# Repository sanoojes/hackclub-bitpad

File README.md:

# BitPad

A simple, customizable macropad with hot swapable keys, fully programmable keys, per-key RGB
lighting, multiple profiles for gaming, programming, editing, and more. uses QMK Firmware

## CAD

## PCB

## Firmware

Firmware available at [firmware/](firmware/) firmware will be tweaked and updated after i get the materials.

## BOM (Bill of materials)

Here's what I used for the device:

- 1x XIAO_RP2040 module
- 1x SK6812 Mini LEDs
- 1x EC11 Rotary Encoder
- 4x M3x16mm screws
- 4x M3x5mmx4mm inserts
- 16x Cherry MX Hotswappable Switches
- 16x DSA Keycaps
- 3D Printed Case

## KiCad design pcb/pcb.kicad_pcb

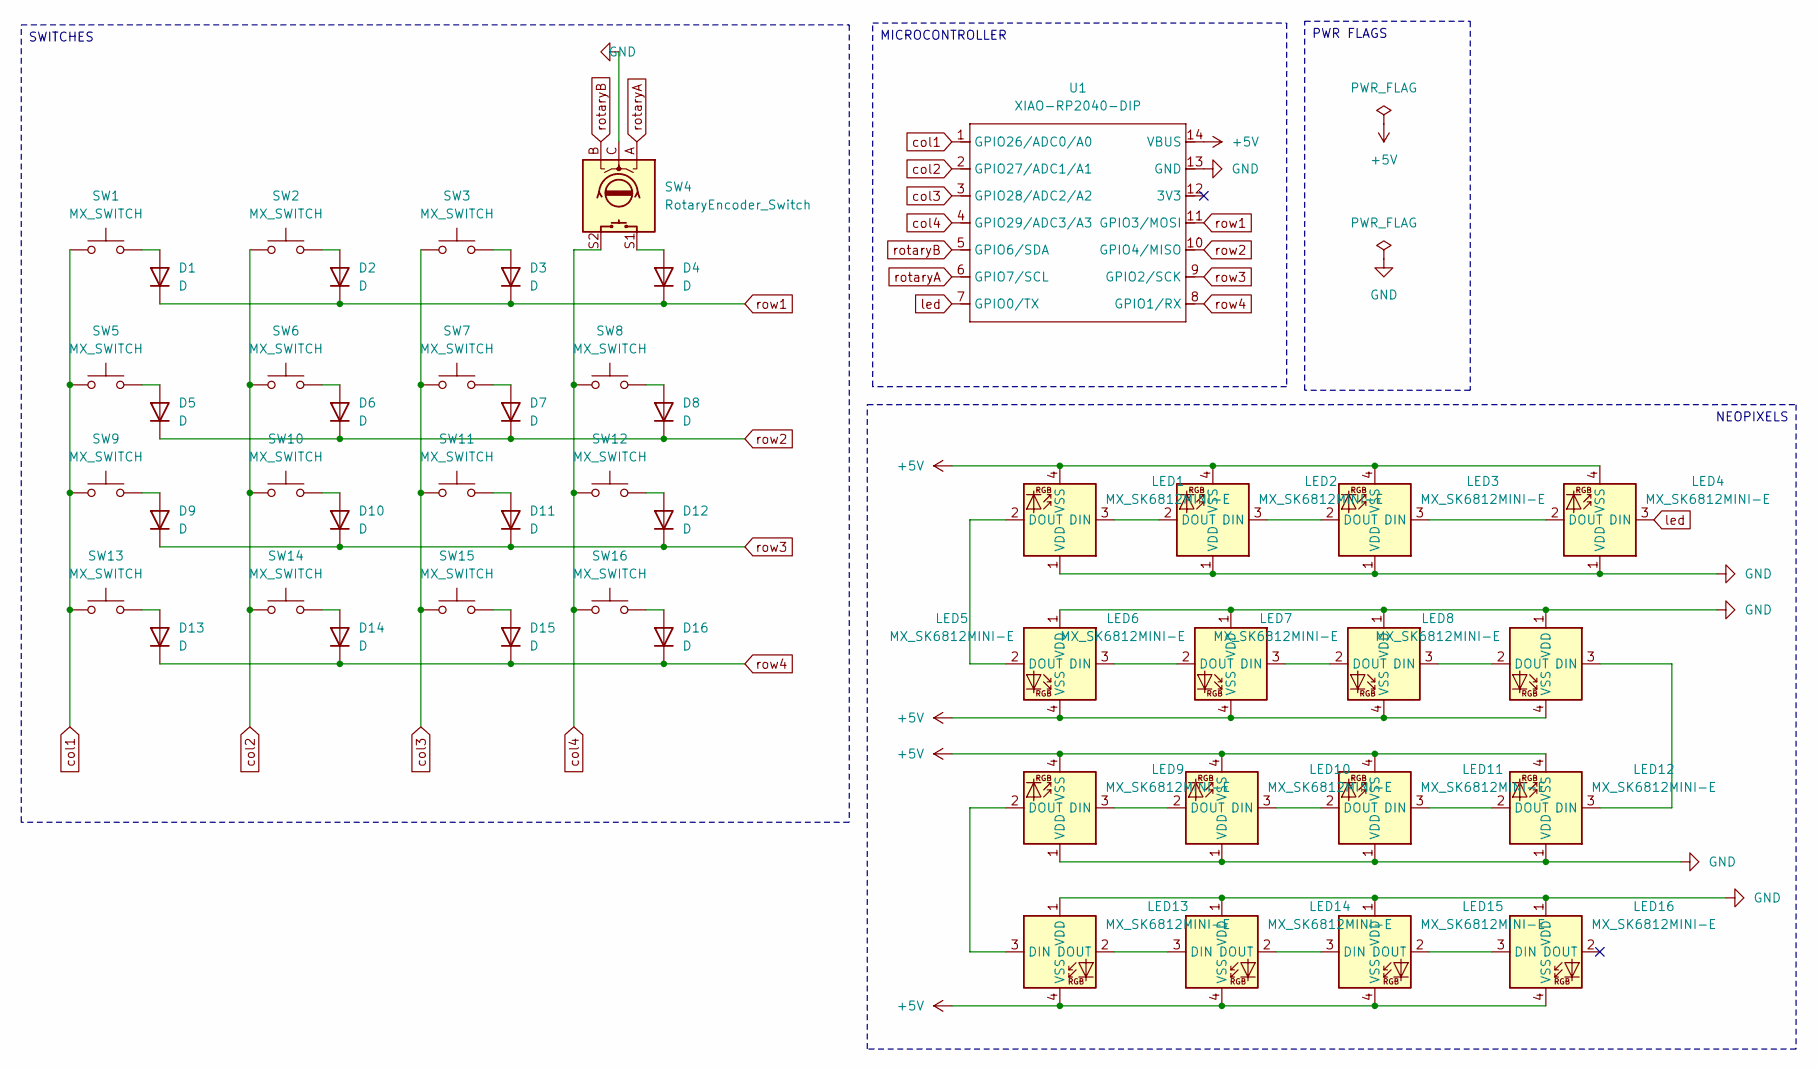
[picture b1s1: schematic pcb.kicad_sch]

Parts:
D1, D2, D3, D4, D5, D6, D7, D8, D9, D10, D11, D12, D13, D14, D15, D16: D; D_DO-35_SOD27_P7.62mm_Horizontal
LED1, LED2, LED3, LED4, LED5, LED6, LED7, LED8, LED9, LED10, LED11, LED12, LED13, LED14, LED15, LED16: MX_SK6812MINI-E; LED_MX_6028R
SW1, SW2, SW3, SW5, SW6, SW7, SW8, SW9, SW10, SW11, SW12, SW13, SW14, SW15, SW16: MX_SWITCH; SW_MX_HS_CPG151101S11_1u
SW4: RotaryEncoder_Switch; RotaryEncoder_Alps_EC11E-Switch_Vertical_H20mm
U1: XIAO-RP2040-DIP

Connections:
+5V: LED1.4 (VSS), LED2.4 (VSS), LED3.4 (VSS), LED4.4 (VSS), LED5.4 (VSS), LED6.4 (VSS), LED7.4 (VSS), LED8.4 (VSS), LED9.4 (VSS), LED10.4 (VSS), LED11.4 (VSS), LED12.4 (VSS), LED13.4 (VSS), LED14.4 (VSS), LED15.4 (VSS), LED16.4 (VSS), U1.14 (VBUS)
GND: LED1.1 (VDD), LED2.1 (VDD), LED3.1 (VDD), LED4.1 (VDD), LED5.1 (VDD), LED6.1 (VDD), LED7.1 (VDD), LED8.1 (VDD), LED9.1 (VDD), LED10.1 (VDD), LED11.1 (VDD), LED12.1 (VDD), LED13.1 (VDD), LED14.1 (VDD), LED15.1 (VDD), LED16.1 (VDD), SW4.C, U1.13 (GND)
unnamed: D1.2 (A), SW1.2
unnamed: D2.2 (A), SW2.2
unnamed: D3.2 (A), SW3.2
unnamed: D4.2 (A), SW4.S1
unnamed: D5.2 (A), SW5.2
unnamed: D6.2 (A), SW6.2
unnamed: D7.2 (A), SW7.2
unnamed: D8.2 (A), SW8.2
unnamed: D9.2 (A), SW9.2
unnamed: D10.2 (A), SW10.2
unnamed: D11.2 (A), SW11.2
unnamed: D12.2 (A), SW12.2
unnamed: D13.2 (A), SW13.2
unnamed: D14.2 (A), SW14.2
unnamed: D15.2 (A), SW15.2
unnamed: D16.2 (A), SW16.2
unnamed: LED1.3 (DIN), LED2.2 (DOUT)
unnamed: LED1.2 (DOUT), LED5.2 (DOUT)
unnamed: LED2.3 (DIN), LED3.2 (DOUT)
unnamed: LED3.3 (DIN), LED4.2 (DOUT)
unnamed: LED5.3 (DIN), LED6.2 (DOUT)
unnamed: LED6.3 (DIN), LED7.2 (DOUT)
unnamed: LED7.3 (DIN), LED8.2 (DOUT)
unnamed: LED10.3 (DIN), LED11.2 (DOUT)
unnamed: LED9.3 (DIN), LED10.2 (DOUT)
unnamed: LED11.3 (DIN), LED12.2 (DOUT)
unnamed: LED8.3 (DIN), LED12.3 (DIN)
unnamed: LED9.2 (DOUT), LED13.3 (DIN)
unnamed: LED13.2 (DOUT), LED14.3 (DIN)
unnamed: LED14.2 (DOUT), LED15.3 (DIN)
unnamed: LED15.2 (DOUT), LED16.3 (DIN)
col1: SW1.1, SW5.1, SW9.1, SW13.1, U1.1 (GPIO26/ADC0/A0)
col2: SW2.1, SW6.1, SW10.1, SW14.1, U1.2 (GPIO27/ADC1/A1)
col3: SW3.1, SW7.1, SW11.1, SW15.1, U1.3 (GPIO28/ADC2/A2)
col4: SW4.S2, SW8.1, SW12.1, SW16.1, U1.4 (GPIO29/ADC3/A3)
led: LED4.3 (DIN), U1.7 (GPIO0/TX)
rotaryA: SW4.A, U1.6 (GPIO7/SCL)
rotaryB: SW4.B, U1.5 (GPIO6/SDA)
row1: D1.1 (K), D2.1 (K), D3.1 (K), D4.1 (K), U1.11 (GPIO3/MOSI)
row2: D5.1 (K), D6.1 (K), D7.1 (K), D8.1 (K), U1.10 (GPIO4/MISO)
row3: D9.1 (K), D10.1 (K), D11.1 (K), D12.1 (K), U1.9 (GPIO2/SCK)
row4: D13.1 (K), D14.1 (K), D15.1 (K), D16.1 (K), U1.8 (GPIO1/RX)

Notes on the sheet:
PWR FLAGS
SWITCHES
NEOPIXELS
MICROCONTROLLER

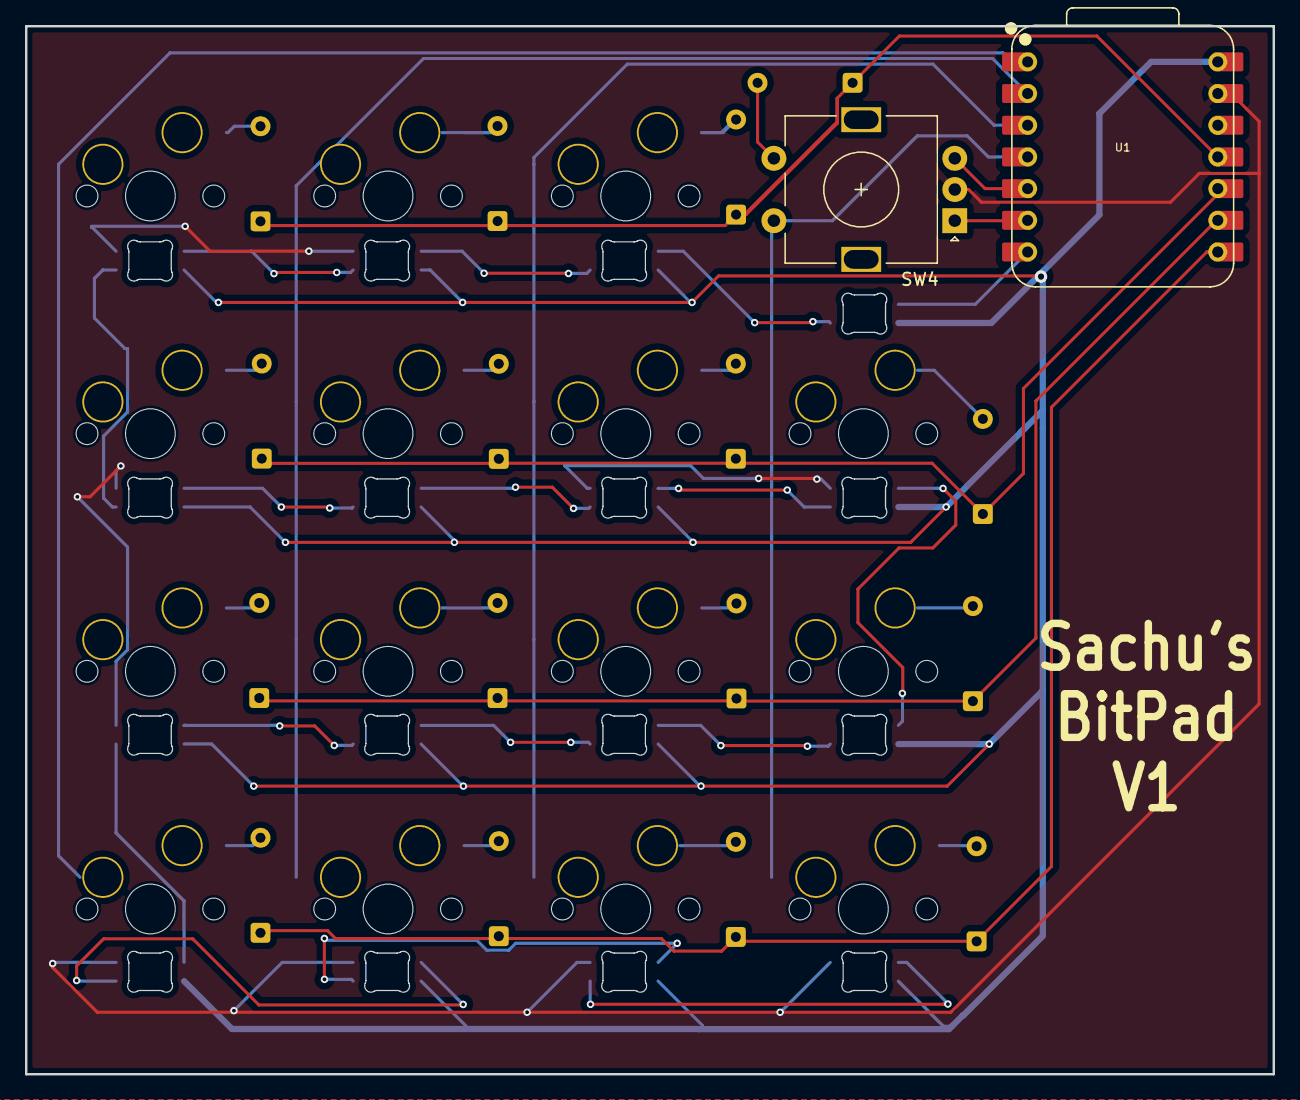
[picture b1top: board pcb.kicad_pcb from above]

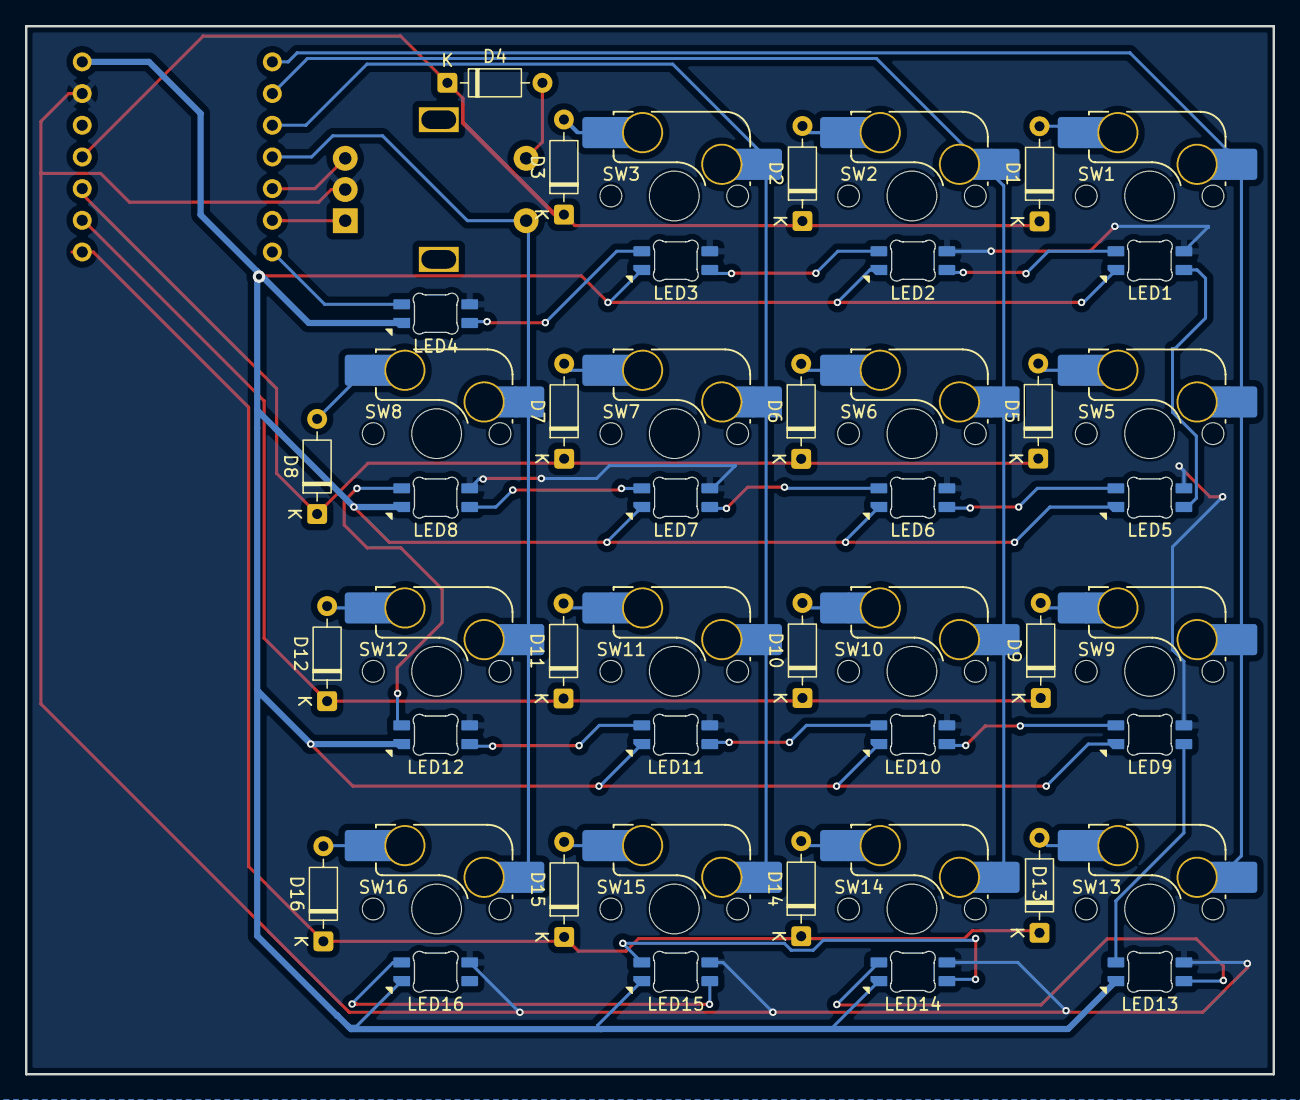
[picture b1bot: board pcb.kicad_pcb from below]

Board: 2 copper layers, 100.0 x 84.0 mm, 49 parts (47 on the bottom side), 44 nets.

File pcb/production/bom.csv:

Designator,Footprint,Quantity,Value,LCSC Part #
"D1, D10, D11, D12, D13, D14, D15, D16, D2, D3, D4, D5, D6, D7, D8, D9",D_DO-35_SOD27_P7.62mm_Horizontal,16,D,
"LED1, LED10, LED11, LED12, LED13, LED14, LED15, LED16, LED2, LED3, LED4, LED5, LED6, LED7, LED8, LED9",LED_MX_6028R,16,MX_SK6812MINI-E,
"SW1, SW10, SW11, SW12, SW13, SW14, SW15, SW16, SW2, SW3, SW5, SW6, SW7, SW8, SW9",SW_MX_HS_CPG151101S11_1u,15,MX_SWITCH,
SW4,RotaryEncoder_Alps_EC11E-Switch_Vertical_H20mm,1,RotaryEncoder_Switch,
U1,XIAO-RP2040-DIP,1,XIAO-RP2040-DIP,

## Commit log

2025-12-15 init: initial commit
2025-12-15 add 3d model for the xiao
2025-12-15 add case and pcb libraries
2025-12-15 update docs
2025-12-15 readme update
2025-12-15 feat: add step file for the case
2025-12-16 feat: add top plate
2025-12-19 update schematics and footprints to match sk6812mini-e
